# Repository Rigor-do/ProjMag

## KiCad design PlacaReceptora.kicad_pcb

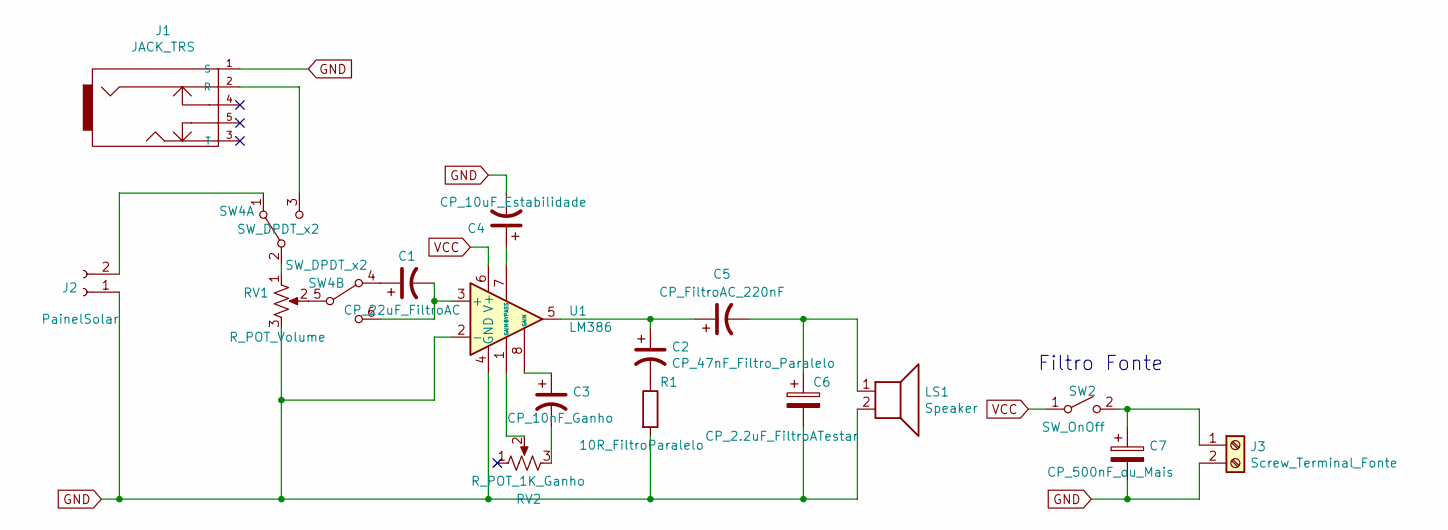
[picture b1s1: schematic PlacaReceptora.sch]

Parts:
C1: CP_22uF_FiltroAC; CP_Radial_Tantal_D6.0mm_P5.00mm
C2: CP_47nF_Filtro_Paralelo; CP_Radial_Tantal_D6.0mm_P5.00mm
C3: CP_10nF_Ganho; CP_Radial_Tantal_D6.0mm_P5.00mm
C4: CP_10uF_Estabilidade; CP_Radial_Tantal_D6.0mm_P5.00mm
C5: CP_FiltroAC_220nF; CP_Radial_Tantal_D6.0mm_P5.00mm
C6: CP_2.2uF_FiltroATestar; CP_Radial_Tantal_D6.0mm_P5.00mm
C7: CP_500nF_ou_Mais; CP_Radial_Tantal_D6.0mm_P5.00mm
J1: JACK_TRS; Tayda_3.5mm_stereo_TRS_jack_A-853
J2: PainelSolar; TerminalBlock_bornier-2_P5.08mm
J3: Screw_Terminal_Fonte; TerminalBlock_bornier-2_P5.08mm
LS1: Speaker; TerminalBlock_bornier-2_P5.08mm
R1: 10R_FiltroParalelo; R_Axial_DIN0309_L9.0mm_D3.2mm_P12.70mm_Horizontal
RV1: R_POT_Volume; Potentiometer_Piher_PC-16_Single_Vertical
RV2: R_POT_1K_Ganho; Potentiometer_Trimmer_ACP_CA9v_Horizontal_Px10.0mm_Py5.0mm
SW2: SW_OnOff; BotaoOnOffMenor
SW4: SW_DPDT_x2; SW_7x7_6Pinos
U1: LM386; DIP-8_W7.62mm_LongPads

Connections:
GND: C4.2, C6.2, C7.2, J1.1 (S), J2.1, J3.2, LS1.2, R1.2, RV1.3, U1.2 (-), U1.4 (GND)
unnamed: C1.1, SW4.4 (A)
unnamed: C1.2, SW4.6 (C), U1.3 (+)
unnamed: C2.1, C5.1, U1.5
unnamed: C2.2, R1.1
unnamed: C3.1, U1.8 (GAIN)
unnamed: C3.2, RV2.3
unnamed: C4.1, U1.7 (BYPASS)
unnamed: C5.2, C6.1, LS1.1
unnamed: C7.1, J3.1, SW2.2 (B)
unnamed: J1.2 (R), SW4.3 (C)
unnamed: J2.2, SW4.1 (A)
unnamed: RV1.1, SW4.2 (B)
unnamed: RV1.2, SW4.5 (B)
unnamed: RV2.2, U1.1 (GAIN)
VCC: SW2.1 (A), U1.6 (V+)

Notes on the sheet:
Filtro Fonte

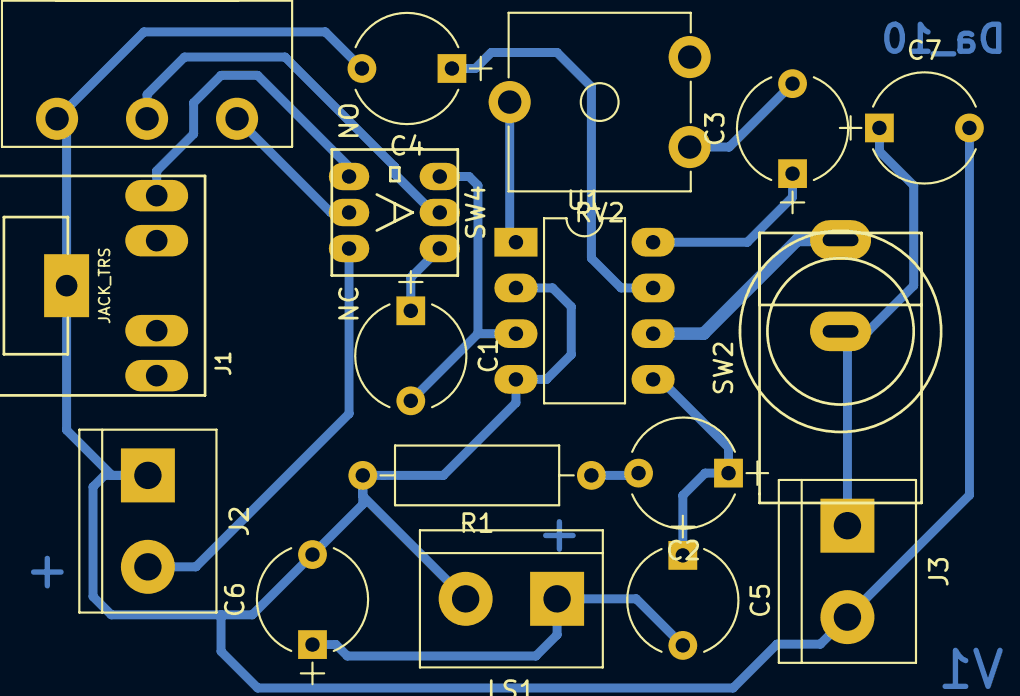
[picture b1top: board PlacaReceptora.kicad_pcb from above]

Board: 2 copper layers, 17 parts (0 on the bottom side), 16 nets.

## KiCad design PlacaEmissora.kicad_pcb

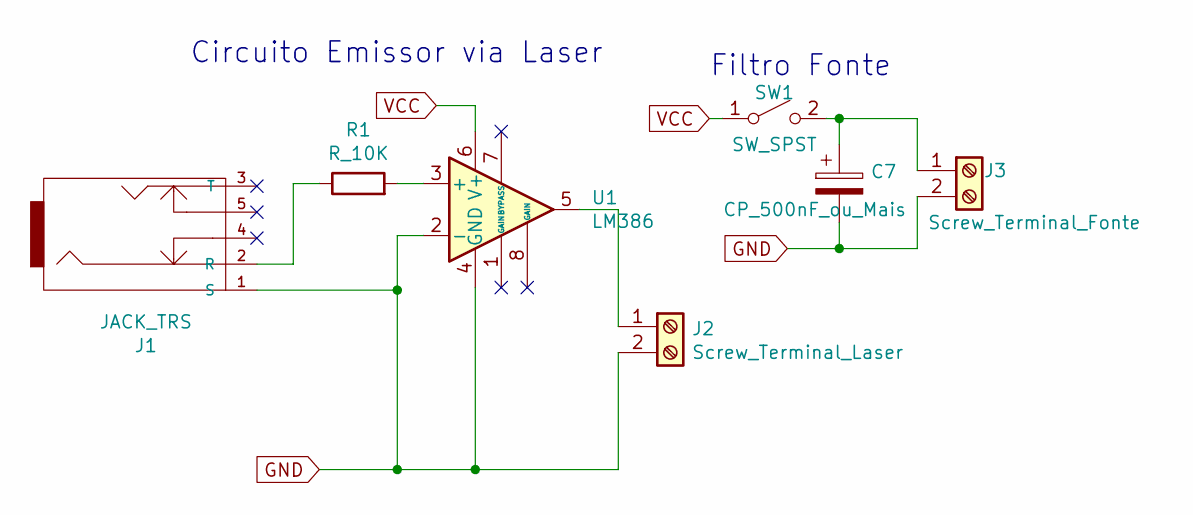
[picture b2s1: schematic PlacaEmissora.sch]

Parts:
C7: CP_500nF_ou_Mais; CP_Radial_D5.0mm_P2.50mm
J1: JACK_TRS; Tayda_3.5mm_stereo_TRS_jack_A-853
J2: Screw_Terminal_Laser; TerminalBlock_bornier-2_P5.08mm
J3: Screw_Terminal_Fonte; TerminalBlock_bornier-2_P5.08mm
R1: R_10K; R_Axial_DIN0207_L6.3mm_D2.5mm_P10.16mm_Horizontal
SW1: SW_SPST; BotaoOnOffMenor
U1: LM386; DIP-8_W7.62mm_LongPads

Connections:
GND: C7.2, J1.1 (S), J2.2, J3.2, U1.2 (-), U1.4 (GND)
unnamed: C7.1, J3.1, SW1.2 (B)
unnamed: J1.2 (R), R1.1
unnamed: J2.1, U1.5
unnamed: R1.2, U1.3 (+)
VCC: SW1.1 (A), U1.6 (V+)

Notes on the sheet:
Filtro Fonte
Circuito Emissor via Laser

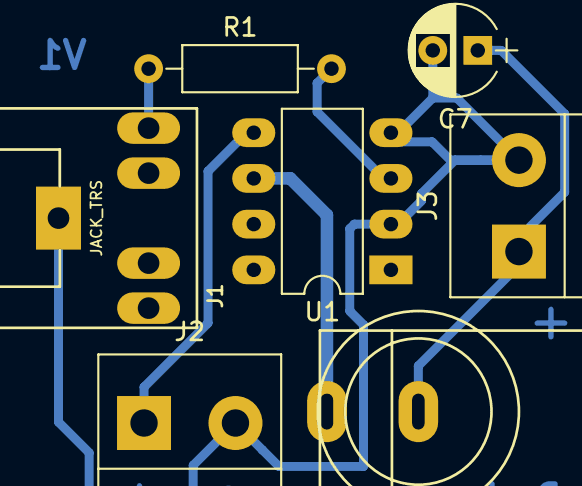
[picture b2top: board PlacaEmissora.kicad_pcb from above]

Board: 2 copper layers, 7 parts (0 on the bottom side), 6 nets.

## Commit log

2019-11-26 Feito os esquemáticos e Adicionado o Botão 7x7mm
    Feito um esquemático temporário para os circuitos emissor e receptor. Ainda serão feitos mais testes.
2019-11-26 Adicionado Botao na placa emissao
2019-11-26 Feito as pcbs dos circuitos emissor e receptor
    Feito os fotolitos da versão V1
